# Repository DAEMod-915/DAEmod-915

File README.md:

# DAEMod-915
Bradley University senior capstone project by Peter Handler, Connor Dickey, and Philip Pierce for a 915MHz ISM open-source and open-hardware digital transceiver implementing Digital radio modes that uses a configurable duty cycle compared to the proprietary alternative LoRa. The goal is to create an example board for digital radio communication. Our design focuses on extensible and easy communication which is configurable to specific use cases like a remote trail camera system or a modernized pager system. We chose low-cost and ubiquitous hardware to build a sustainable platform. Overall, this repository showcases the potential use cases of a finalized product

For more information please read all the existing [documentation](./docs/) about the project.

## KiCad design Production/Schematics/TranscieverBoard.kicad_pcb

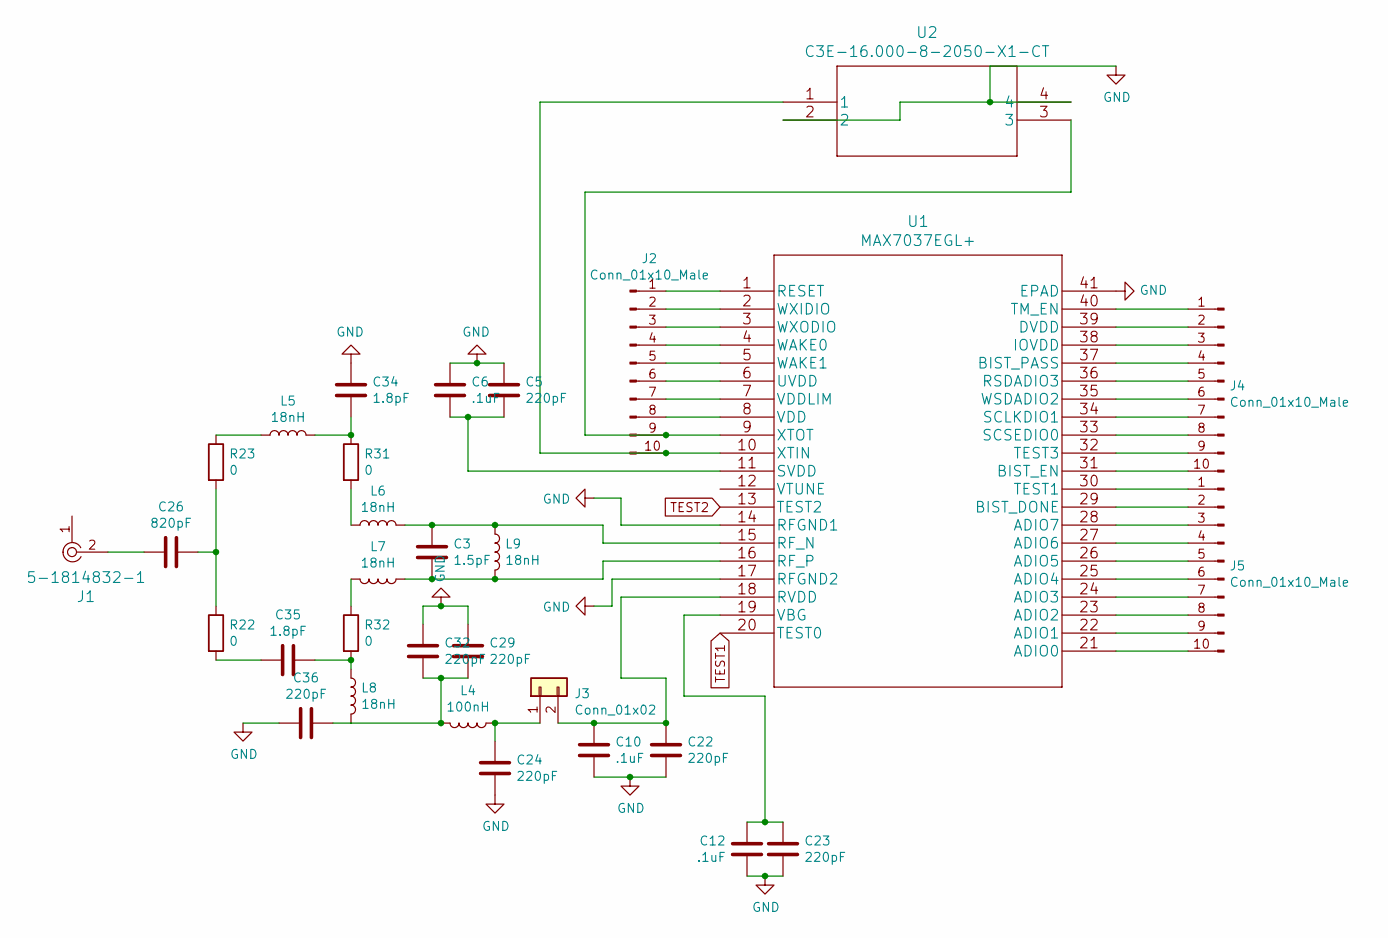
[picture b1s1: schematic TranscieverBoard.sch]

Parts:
C3: 1.5pF; C_0402_1005Metric
C5, C22, C23, C24, C29, C32, C36: 220pF; C_0402_1005Metric
C6, C10, C12: .1uF; C_0603_1608Metric
C26: 820pF; C_0603_1608Metric
C34, C35: 1.8pF; C_0402_1005Metric
J1: 5-1814832-1; RF_SMA_Vertical_5-1814832-1; MPN 5-1814832-1; Digi-Key_PN A97594-ND
J2, J4, J5: Conn_01x10_Male; PinHeader_1x10_P2.54mm_Vertical
J3: Conn_01x02; PinHeader_1x02_P2.54mm_Vertical
L4: 100nH; L_0402_1005Metric
L5, L6, L7, L8, L9: 18nH; L_0402_1005Metric
R22, R23, R31, R32: 0; R_0402_1005Metric
U1: MAX7037EGL+; MAX7037EGL&plus_
U2: C3E-16.000-8-2050-X1-CT

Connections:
GND: C5.1, C6.1, C10.2, C12.2, C22.2, C23.2, C24.2, C29.1, C32.1, C34.2, C36.2, U1.14 (RFGND1), U1.17 (RFGND2), U1.41 (EPAD), U2.2, U2.4
unnamed: C3.1, L6.2, L9.1, U1.15 (RF_N)
unnamed: C3.2, L7.1, L9.2, U1.16 (RF_P)
unnamed: C5.2, C6.2, U1.11 (SVDD)
unnamed: C10.1, C22.1, J3.2, U1.18 (RVDD)
unnamed: C12.1, C23.1, U1.19 (VBG)
unnamed: C24.1, J3.1, L4.1
unnamed: C26.1, R22.1, R23.2
unnamed: C26.2, J1.2
unnamed: C29.2, C32.2, C36.1, L4.2, L8.2
unnamed: C34.1, L5.2, R31.1
unnamed: C35.1, L8.1, R32.2
unnamed: C35.2, R22.2
unnamed: J2.1, U1.1 (RESET)
unnamed: J2.2, U1.2 (WXIDIO)
unnamed: J2.3, U1.3 (WXODIO)
unnamed: J2.4, U1.4 (WAKE0)
unnamed: J2.5, U1.5 (WAKE1)
unnamed: J2.6, U1.6 (UVDD)
unnamed: J2.7, U1.7 (VDDLIM)
unnamed: J2.8, U1.8 (VDD)
unnamed: J2.9, U1.9 (XTOT), U2.3
unnamed: J2.10, U1.10 (XTIN), U2.1
unnamed: J4.1, U1.40 (TM_EN)
unnamed: J4.2, U1.39 (DVDD)
unnamed: J4.3, U1.38 (IOVDD)
unnamed: J4.4, U1.37 (BIST_PASS)
unnamed: J4.5, U1.36 (RSDADIO3)
unnamed: J4.6, U1.35 (WSDADIO2)
unnamed: J4.7, U1.34 (SCLKDIO1)
unnamed: J4.8, U1.33 (SCSEDIO0)
unnamed: J4.9, U1.32 (TEST3)
unnamed: J4.10, U1.31 (BIST_EN)
unnamed: J5.1, U1.30 (TEST1)
unnamed: J5.2, U1.29 (BIST_DONE)
unnamed: J5.3, U1.28 (ADIO7)
unnamed: J5.4, U1.27 (ADIO6)
unnamed: J5.5, U1.26 (ADIO5)
unnamed: J5.6, U1.25 (ADIO4)
unnamed: J5.7, U1.24 (ADIO3)
unnamed: J5.8, U1.23 (ADIO2)
unnamed: J5.9, U1.22 (ADIO1)
unnamed: J5.10, U1.21 (ADIO0)
unnamed: L5.1, R23.1
unnamed: L6.1, R31.2
unnamed: L7.2, R32.1
TEST1: U1.20 (TEST0)
TEST2: U1.13 (TEST2)

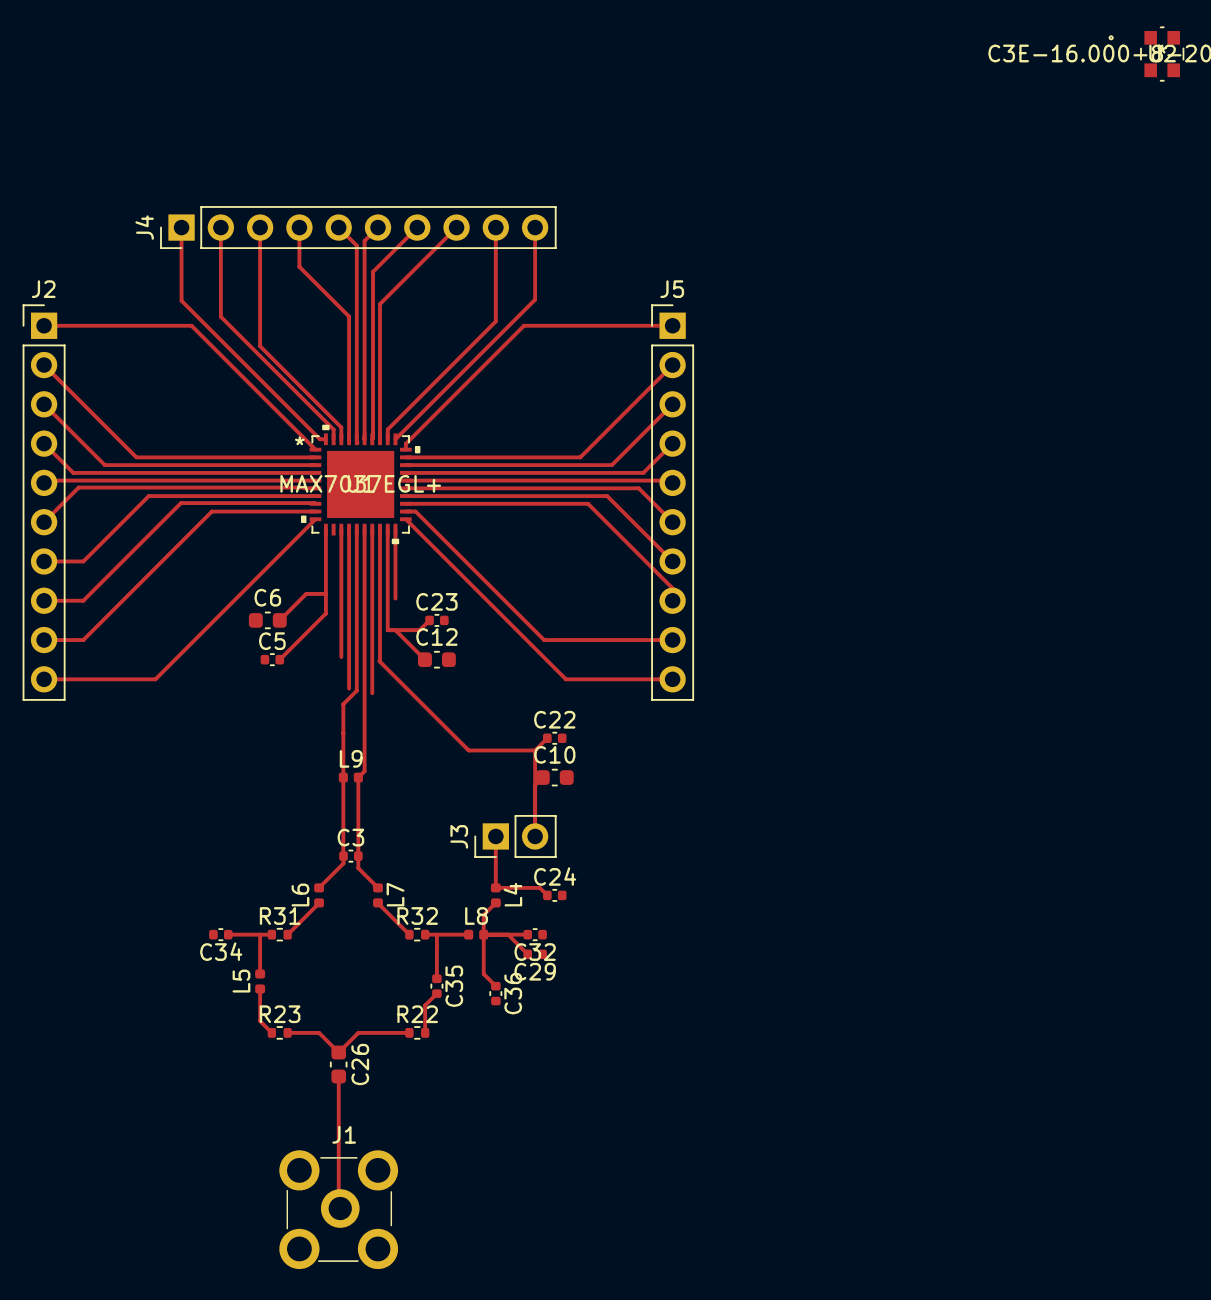
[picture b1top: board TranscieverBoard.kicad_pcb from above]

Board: 2 copper layers, 31 parts (0 on the bottom side), 46 nets.

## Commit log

2022-01-24 First commit test and update README with an intro
2022-02-02 Addition of MAX7037 Design Files
    Added MAX7037 KiCad Files
    Added /Production
    Added /Production/Schematics
    Added /Production/Parts_Library
2022-02-13 Gerber Files Generated
    Gerber Files for transceiver module PCB generated
2022-02-13 Updated PCB
    Updated PCB from MCX to SMA
2022-02-13 PCB Design update
    PCB schematic update
2022-05-15 Removal of legacy files
2022-06-03 Added EFR32 Submodule
2022-06-03 Fall Semester Whitepaper.
2022-06-03 Fall Semester Proposal Presentation with multiple formats.
2022-06-03 Spring Semester Presentation with multiple formats.
2022-06-03 Final Version of Poster.
2022-06-03 Revert README Deletion and added Location for Reading Materials
2022-06-03 Added gitignore File and gitmodules
2022-06-03 Add ESP32 submodule.

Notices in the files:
parts and their libraries:
Copyright 2021 Accelerated Designs. All rights reserved.
